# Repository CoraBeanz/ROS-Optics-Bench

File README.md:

<p align="center">
  <img src="docs/images/hero.svg" width="100%" alt="Self-Aligning Laser-to-Fiber Bench. Seen from above, a 635 nm laser beam passes an aperture, two polarizers and a beamsplitter, folds off two motorized mirrors, M1 and M2, and is focused into a single-mode fiber. M1 gets knocked, the focused spot slides off the fiber's core and the coupling drops to almost nothing; M2's motors search until the light comes back, then both mirrors walk the beam back to its peak. A fiber-face inset shows the spot stepping outward in a square spiral beside the core until it finds it, and a chart plots the output-to-reference photodiode ratio, as a share of its peak, through the knock and the recovery, replayed from the bench twin simulator.">
</p>

<h3 align="center">A mostly 3D-printed optical bench that couples a 635 nm laser into an optical fiber by itself. Knock a mirror out of line and four stepper-driven adjusters steer the beam back to peak coupling, with no hands on the knobs.</h3>

<p align="center">

</p>

<p align="center">
  <a href="#how-it-works"><b>How it works</b></a> ·
  <a href="#the-bench"><b>The bench</b></a> ·
  <a href="#optical-path"><b>Optical path</b></a> ·
  <a href="#auto-align"><b>Auto-align</b></a> ·
  <a href="#electronics"><b>Electronics</b></a> ·
  <a href="#software"><b>Software</b></a> ·
  <a href="#roadmap"><b>Roadmap</b></a> ·
  <a href="docs/bom/README.md"><b>Parts list</b></a>
</p>

## How it works

Getting a laser into a single-mode fiber means landing a focused spot on a core a few microns across, at the right angle. By hand that takes two kinematic mirrors, four knobs and a lot of patience. Here a NEMA 8 stepper turns each knob, and two photodiodes tell the motors how close they are.

| 1 · Score the coupling | 2 · Find the light | 3 · Steer and walk |
|---|---|---|
| A beamsplitter sends part of the laser to a reference photodiode, and the fiber's output lands on a second one. Their ratio is the score, so laser flicker cancels out. | After a knock the spot has usually left the core and the output reads nothing. M2 steps the spot outward in a square spiral until the output photodiode sees light again. | M2 alone moves the spot across the core. M1 with a matched, opposite M2 move changes only the angle. Alternating the two climbs the long, thin peak that one-knob-at-a-time adjusting stalls on. |

## The bench

<table>
  <tr>
    <td width="50%" valign="top">
      
      <br><sub>Laser, polarizer and beamsplitter, then M1 and M2, each with two NEMA 8 motors turning its adjusters through brass couplers and hex rods.</sub>
    </td>
    <td valign="top">

**Light.** A 635 nm Quarton laser module under 1 mW, trimmed by a 2 mm printed aperture and dimmed by two crossed polarizers.

**Steering.** Two 1 in mirrors in Thorlabs KMS-style kinematic mounts. A NEMA 8 stepper turns each 100 TPI adjuster through a brass coupler and a 2 mm hex rod: four motorized axes, 79 nm of screw travel per microstep.

**Focus.** An f = 8 mm asphere on a micrometer stage focuses the beam onto a fixed FC bulkhead. The lens moves; the fiber stays put.

**Sensing.** BPW34 photodiodes on MCP6002 transimpedance amps, read by a 16-bit ADS1115.

**Control.** An ESP32 Feather V2 drives four TMC2209s on one UART bus and takes plain-text commands over USB from a desktop test panel or from ROS 2 on a Jetson.

**Base.** Printed breadboard tiles on a 25 mm hole grid, so parts come off and go back in the same place.

  </td>
  </tr>
</table>

The full CAD model is one STEP file exported from Onshape with its subassembly tree, [`cad/assemblies/ros_laser_bench_main_assembly.step`](cad/assemblies/README.md). Every part to buy, print or check is in the [parts list](docs/bom/README.md) (source: `docs/bom/bom.csv`).

## Optical path

The beam folds in a Z. M1 and M2 sit 150 mm apart, and M2 is 310 mm from the lens, so tilting the two mirrors together can set both where the beam crosses the lens and the angle it arrives at, and through them where the focused spot lands on the fiber face and the angle it enters at. One microstep tilts a mirror by about 4.6 µrad. One turn of M2's X adjuster moves the spot about 230 µm across the fiber face, and one turn of its Y adjuster about 165 µm, because at a 45° fold a vertical tilt bends the beam by √2 times the tilt instead of twice it.

The 2 mm aperture does mode matching. The laser's 7 x 3 mm beam is much bigger than the single-mode fiber's mode seen at the lens (1.5 mm across), so only its centre can couple. In the bench twin 83% of the light through the aperture couples, against 25% of the whole beam without it. The fiber gets about a quarter of the laser's power either way, but with the aperture the light that could never couple is stopped before the beamsplitter, so the out/ref score at the peak is 0.67 instead of 0.20. In phase 1 the OV9281's bare sensor takes the lens's place, and with the two irises it lets the mirrors put the beam on the lens axis by spot position before the lens and fiber go in.

## Auto-align

With a single-mode fiber the coupling depends on where the spot lands on the core (set by the beam's angle at the lens) and on the angle it comes in at (set by the beam's offset at the lens). The first is about 25 times more sensitive, and both mirrors change both, so in motor coordinates the peak is a ridge 23 times longer than it is wide, running diagonally across M1 and M2. Turning one knob at a time crawls along it. Auto-align, in the [test panel](#bench-test-panel) and as a [ROS 2 action](#ros-2-on-the-jetson), uses the two moves people use by hand instead:

- **Find.** If the output photodiode sees nothing, M2 steps the spot outward in a square spiral, up to **Search (turns)** either way, until the out/ref ratio clears 2% of its aligned value.
- **Steer.** M2 alone moves the spot across the core: the narrow direction, 25 microsteps to the 1/e point on M2X.
- **Walk.** M1 plus a matched, opposite M2 move keeps the spot where it is and changes only the angle: the wide direction, about 580 microsteps of M1.
- **Repeat** walk and steer on both planes until a sweep gains less than 0.3%. Each line search approaches its points from the same side, so the play in the hex couplings always sits the same way.

The first run on a fiber also measures the walk directions on the real bench, since they depend on motor directions and lever arms. In 100 simulated knocks of 0.3 to 3 mrad, steer and walk brought all 100 back above 99.9% of the best coupling, with a median of 19 s and a worst case of 66 s. One motor at a time got 59 back to 90%. Everything here comes from the [bench twin](#bench-twin-simulator); Auto-align hasn't run on the hardware yet.

## Electronics

| Part | Role |
| --- | --- |
| Adafruit ESP32 Feather V2 | Real-time side: steppers, soft limits, photodiode sampling, laser |
| 4x Adafruit TMC2209 breakout on one UART bus | Stepper drivers: 3200 microsteps per adjuster turn, StealthChop, current set over UART |
| ADS1115 (16-bit ADC) + 2x BPW34 photodiode on an MCP6002 transimpedance amp (47 kΩ) | Reference and output power |
| 12 V supply | Motor power; the Feather runs from USB |
| Jetson (ROS 2) | Camera, optimizer, experiment control |
| Arducam OV9281 (global shutter, UVC) | Bare-sensor beam profiler for phase 1 |

<table>
  <tr>
    <td width="58%"></td>
    <td width="42%"></td>
  </tr>
  <tr>
    <td><sub>Control board, 100 x 100 mm, two layers. The Feather, the four TMC2209 breakouts and the ADS1115 plug in.</sub></td>
    <td><sub>Photodiode amp, 34 x 25 mm. Build two: reference and output.</sub></td>
  </tr>
</table>

Both boards are KiCad 10 projects generated from Python, all through-hole, with Gerbers ready to order in [electronics/pcb](electronics/pcb/README.md). Every cable on the bench is in [electronics/system_wiring.svg](electronics/system_wiring.svg), and the full pin table is in [electronics/wiring.md](electronics/wiring.md).

## Software

Where each piece lives, and how far it has been run:

| Module | What it does | Run so far |
| --- | --- | --- |
| [`firmware/optics_bench`](#building-the-firmware) | Arduino IDE sketch for the ESP32: four axes with soft limits and positions kept in flash, auto-ranging photodiode sampling, the laser, and the serial protocol | On the bench: laser, all four motors and both photodiodes |
| [`tools/test_gui.py`](#bench-test-panel) | Dark-mode PySide6 test panel: jog, go-to, photodiode readout and plots, CSV logging and Auto-align; `--sim` runs it on the bench twin | On the bench; Auto-align on the simulator only |
| [`tools/bench_twin`](#bench-twin-simulator) | Physical model of the bench and the Aligner both front ends run; `tools/twin.py` runs trials and draws figures | 14 unit tests |
| [`host/ros2_ws`](#ros-2-on-the-jetson) | ROS 2 Humble packages for the Jetson: the bench as topics, services and actions, Align as an action, and a beam-spot node for the OV9281 | Against the simulator on Humble |

### Building the firmware

1. In the Arduino IDE, install the ESP32 boards package (Boards Manager, "esp32" by Espressif).
2. Install the libraries below with the Library Manager.
3. Open `firmware/optics_bench/optics_bench.ino`.
4. Select your ESP32 board and port, then Upload. Serial Monitor runs at 115200 baud with newline line endings.

Code in `src/` is compiled with the sketch automatically. Record any library added through the Library Manager here so the build can be reproduced.

| Library | Version | Used for |
| --- | --- | --- |
| TMCStepper (teemuatlut) | 0.7.3 | TMC2209 register setup over UART |
| AccelStepper (Mike McCauley) | 1.64 | Ramped STEP/DIR motion |

The ADS1115 photodiode ADC is read with the ESP32 core's own Wire library (`src/sensing/sensing.cpp`), so it needs no library of its own. Firmware 0.1.0 used Adafruit ADS1X15 2.6.2 and Adafruit BusIO for it; they can stay installed but are no longer used.

The firmware was last built with the esp32 boards package 3.3.7.

Every pin is set in `firmware/optics_bench/config.h`. The wiring diagram and full pin table for the Feather ESP32 V2, the four Adafruit TMC2209 breakouts, the laser, the ADS1115 and the two photodiode amplifier boards are in [electronics/wiring.md](electronics/wiring.md). The serial protocol is plain text and documented in `firmware/optics_bench/src/comms/protocol.h`, so the Serial Monitor or the Jetson can use the same commands.

### Bench test panel

`tools/test_gui.py` is a small desktop app for the bench tests: laser on/off, jog, nudge and go-to for the four mirror motors, and live photodiode readings. It is a dark-mode Qt window built on PySide6 (the LGPL Qt binding) and pyserial, both listed in `tools/requirements.txt`.

```
py -3 -m pip install -r tools/requirements.txt
py -3 tools/test_gui.py          # pick the ESP32's COM port, Connect
py -3 tools/test_gui.py --sim    # try it without hardware
```

`py -3` picks the regular Python install on Windows; a bare `python` can resolve to another bundled interpreter such as KiCad's.

- **Positions** are in microsteps, 3200 per adjuster turn. One turn of a 100 TPI adjuster is 254 um, so a full step is about 1.3 um of screw travel.
- **Zero and soft limits.** "Reset to 0" on a motor's row calls its current knob position zero without moving it, and "Reset all to 0" does all four. Use them whenever the stored position has stopped matching reality, for example after turning an adjuster by hand. The soft limits (default -3 to +3 turns, adjustable up to +-8) stay relative to zero, because the hex bit only has about 4 turns of engagement one way. Positions and limits are saved to flash and survive a power cycle. If power drops while a motor is moving, or a motor moves and its driver loses its 12 V before the firmware next sees it working (it checks a few seconds after the motors stop), that motor's position is marked untrusted: the panel warns that positions may be off, and the firmware's boot message names the motors. The mark is kept in flash across reboots until you reset that motor ("Reset to 0") or all four. A 12 V cycle while the motors sit still only warns: the positions are kept, and each motor may settle up to 2 full steps (about 2.5 um of screw travel) away when it is next powered.
- **Coil release.** A motor is powered only while it moves: it is released 0.5 s after it stops, so the motors stay cool between moves, and the non-back-driving adjuster screws hold the mirror. The **On** box shows whether a motor is powered; ticking it holds that motor powered until you untick it. `AUTO_RELEASE` in `config.h` turns this off.
- **Hold-to-jog** (the double arrows) keeps a motor running while the button is held. The firmware stops it by itself if the panel stops refreshing the jog, so a crashed GUI can't run a motor to its limit.
- **Keys:** arrows move M1 (Left/Right = M1X, Down/Up = M1Y), A/D and S/W move M2X and M2Y by the selected step, L toggles the laser, Esc stops everything.
- **Diag** shows the TMC2209 status (current, StealthChop, overtemperature, short and open-load flags). A driver that doesn't answer on the UART shows a red dot and refuses to move. Between moves the firmware checks one driver every 0.25 s, so a driver that loses its 12 V turns red within about a second.
- **Auto-align.** Pick the fiber on the bench and press **Align**. It finds the light, then peaks the out/ref ratio by steering with M2 and walking M1 and M2 together (see [Auto-align](#auto-align)). The first run after connecting or switching fiber also measures the walk directions, so start it near the peak; the panel keeps them until it disconnects. Later runs recover from wherever the beam is, for example after a knock. If there is no light on the output photodiode, it first searches with M2 up to **Search (turns)** either way (default 0.4 turn: about ±90 µm across the fiber face and ±65 µm up and down; one turn of M2X moves the spot about 230 µm, one turn of M2Y about 165 µm). The search covers a square, so its time grows with the square of that number, and the log says how many points it will visit. Soft limits still stop any move that would pass them. **Stop** or Esc ends it. It uses the same serial commands as the rest of the panel, but it has only been run against the simulator so far.
- **Photodiodes.** Tick **Live** to stream the reference and output photodiode voltages (5 to 50 readings a second, each the average of all ADC samples since the last one). The panel shows each voltage with its photocurrent and optical power, the output/reference ratio with the best ratio seen and the motor positions where it happened, and a rolling plot (log scale optional). **Measure dark** switches the laser off briefly, records the offsets and subtracts them from then on. **ADC range** fixes the ADS1115 gain instead of auto-ranging, and **Save CSV** writes up to the last 30,000 readings (10 minutes at 50 a second).
- **Simulator.** `--sim` (or the Simulator port) runs the bench twin behind the same serial commands: the photodiodes read what the modelled optics couple into the chosen fiber, with the best position hidden a little way from zero. **Knock M1** and **Knock M2** tilt a mirror by 0.5 to 2 mrad as if bumped, **Unknock** takes the knocks out, and **Peak?** shows where the best position is. Knock, then Align, to watch it recover. The same commands work from the console as `SIM KNOCK M1 [mrad]`, `SIM PEAK`, `SIM FIBER sm630` and `SIM RESET`.

#### First power-up checklist

1. Flash the firmware and connect. A driver whose 12 V supply is off doesn't answer on the UART, so it shows a red dot, and a move on that axis is refused with "driver offline".
2. With the 12 V supply on, send `REPROBE ALL` (or just move the axis, which retries). The dots should go green, and the REPROBE reply should end in `slots=ok` (the connection bar picks it up on the next `INFO`). Switching the 12 V on after USB like this is fine, and so is switching it off between sessions with USB left on: the positions are kept, though each driver's microstep counter restarts, so a motor may settle up to 2 full steps away when it is next powered. Only a motor that was moving, or had just moved, when its 12 V went away is marked untrusted until you reset it.
3. Take the hex bits out of the adjusters and nudge each motor by 1/4 turn to check which way positive turns. Flip it with `invert` in `config.h` if needed.
4. Refit the bits, press "Reset all to 0", and start aligning.
5. With the ADS1115 and photodiode boards connected, the photodiode panel should show `ADC: ok`. Cover each diode and shine a light on it to check its channel, then press **Measure dark** with the room lit as it will be during runs. If the ADS1115 stops answering later (a loose STEMMA QT cable), the firmware drops the failed readings instead of reporting 0 V, warns `ADS1115 stopped answering` after 10 failures in a row, and stops reading it until the next photodiode request finds it again.

### Bench twin (simulator)

`tools/bench_twin` is a small physical model of the bench, used to size and test the alignment routine before the hardware can. It models:

- **Optics:** the 7 x 3 mm laser beam cut by the 2 mm aperture, the two mirrors 150 mm apart, iris 2 at 3 mm, and the f = 8 mm lens. Single-mode coupling is the overlap of the laser field with the fiber mode, including the aperture's hard edge. Multimode coupling is the share of the focused spot that the core accepts.
- **Motors:** 100 TPI adjusters on a 17.3 mm lever and a little play in each hex coupling. The randomized benches the simulator and the trials use also add a little crosstalk between each mount's two axes.
- **Photodiodes:** the reference and output photodiodes through the ADS1115, with noise and dark offsets.
- **Knocks:** a bumped mirror mount tilts by an amount the motors don't know about.

```
py -3 tools/twin.py                       key numbers (--fiber sm630, mm50 or smf28)
py -3 tools/twin.py ceiling               best coupling vs aperture size and lens focal length
py -3 tools/twin.py trials -n 100 --compare   knock a mirror and recover, 100 times, both methods
py -3 tools/twin.py landscape             redraws docs/images/twin_landscape.png (needs matplotlib)
py -3 -m unittest discover tools/tests
```

What it says so far, for the single-mode fiber:

- **The peak is narrow and diagonal.** Moving M2X alone, coupling falls to 1/e within 25 microsteps (1.5 full steps). Moving M1 and M2 together the opposite way ("walking"), it stays up for about 580 microsteps. So in motor coordinates the peak is a long, thin ridge, 23 times longer than it is wide, running diagonally across M1 and M2. Adjusting one motor at a time stalls part-way along it.
- **Recovery.** In 100 simulated knocks of 0.3 to 3 mrad on a random mirror, steer and walk got all 100 back above 99.9% of the best coupling, with a median of 19 s and a worst case of 66 s (at 60 RPM and 600 RPM/s). One motor at a time got 68 of 100 back to 90%, and its worst case ended at 35%. Most of the time goes into finding the light again. Knocks of M1 above about 5 mrad can defeat the search even though M2 could still put the spot back on the core: the beam then crosses the lens about 1.5 mm off axis and enters the fiber too steeply, so M2 alone brings back under 3% of the peak and the spiral never sees light (11 of the 46 M1 knocks in a run of 100 knocks of 3 to 6 mrad). A larger **Search (turns)** doesn't help these.
- **The 2 mm aperture is close to ideal for coupling efficiency.** With the f = 8 mm lens, 83% of the light that gets through it can be coupled. The best combination tried reaches 86% (a 2.5 mm aperture with f = 11 mm), and 2 mm with f = 9 mm gets 85%. Without the aperture only 25% couples, because the 7 x 3 mm beam is much bigger than the fiber mode seen at the lens (1.5 mm). The aperture passes only 30% of the beam, so the fiber gets about a quarter of the laser's power either way; what it changes is the out/ref ratio at the peak, 0.67 instead of 0.20, since the reference photodiode sits after it.
- **The play in the hex couplings matters.** One degree of play is about 9 microsteps, a third of the single-mode peak's width. Each line search in the routine therefore approaches its points from one side.

The numbers rest on estimates to replace with bench measurements, all set in `tools/bench_twin/bench.py` and `optics.py`:

| Estimate | Value used | How to measure |
| --- | --- | --- |
| Adjuster lever arm | 17.3 mm (from the 24.5 mm motor spacing) | Scan M2X across the peak; the width scales with it |
| Play per hex coupling | 1 degree (9 microsteps) | Hysteresis test: approach the same point from both sides |
| Laser beam | 7 x 3 mm across (taken as the 1/e^2 width) | Camera or knife edge |
| Fiber mode | 4.2 um across (630HP) | Datasheet |
| Lens clear aperture | 5 mm | The lens listing |
| Beamsplitter, laser power, polarizer setting | 50/50, 0.9 mW, 30% | Photodiode volts |

The banner at the top of this page replays one of these runs: M1 knocked 1.5 mrad on the single-mode fiber, recovered in 17 s. The figures are drawn by the scripts in [`docs/images/src`](docs/images/src/common.py); the banner and the Auto-align figure run the twin to get their numbers.

### ROS 2 on the Jetson

`host/ros2_ws` holds ROS 2 Humble packages for the Jetson: a driver node that puts the ESP32 (or the simulator) on ROS topics, services and actions, with Align as an action; a node that finds the laser spot on the OV9281; and launch files. They use `tools/bench_link.py` and `tools/bench_twin` directly, so they align the same way the test panel does. Setup and usage: [host/ros2_ws/README.md](host/ros2_ws/README.md).

```
ros2 launch optics_bench_bringup bench.launch.py                          # on the simulator
ros2 launch optics_bench_bringup bench.launch.py port:=/dev/optics_bench  # on the bench
```

## Roadmap

The laser, all four mirror motors and both photodiodes (on hand-wired amplifiers for now) work on the bench, and first fiber coupling by hand is under way. The PCBs are designed but not ordered yet. Auto-align and the ROS 2 packages have run only against the bench twin so far, and the ROS 2 packages haven't run on the Jetson, the ESP32 or the camera yet.

- [x] Bench CAD in Onshape: printed base, motor-mirror assemblies, optics mounts ([`cad/`](cad/assemblies/README.md))
- [x] Firmware for the laser, the four mirror motors and both photodiodes, and the [test panel](#bench-test-panel), running on the bench
- [x] [Bench twin](#bench-twin-simulator) and Auto-align, tested in simulation over hundreds of knocks
- [x] [ROS 2 Humble packages](#ros-2-on-the-jetson), run against the simulator
- [x] Control board and photodiode amp PCBs designed, with Gerbers ready ([`electronics/pcb`](electronics/pcb/README.md))
- [ ] **Phase 1, beam steering:** the camera and the two irises put the beam on a known axis by spot position
- [ ] **Phase 2, fiber coupling:** swap the camera for the lens and fiber and climb to maximum coupled power, multimode first, then single-mode
- [ ] **Phase 3, the demo:** bump a mirror and watch it recover on the real bench
- [ ] PCBs ordered and built, and ROS 2 running on the Jetson

## Stack

| Layer | Built with |
|---|---|
| **Optics** | 635 nm diode laser, 2 mm aperture, crossed polarizers, 1 in mirrors in kinematic mounts, f = 8 mm asphere, FC fiber |
| **Mechanics** | 3D-printed mounts and base designed in Onshape; NEMA 8 steppers, brass couplers and hex rods on 100 TPI adjusters |
| **Electronics** | ESP32 Feather V2, TMC2209 drivers, ADS1115 and BPW34 photodiodes on MCP6002 amps; KiCad 10 boards generated from Python |
| **Firmware** | C++ Arduino IDE sketch on the ESP32: TMCStepper, AccelStepper, plain-text serial protocol |
| **Desktop** | Python, PySide6 and pyserial: the dark-mode test panel |
| **Simulation** | Python and numpy: Gaussian-beam coupling, motors with play, photodiodes, and the Aligner |
| **Robotics** | ROS 2 Humble on a Jetson: driver node with Align and MoveTo actions, v4l2_camera and a beam-spot node |

## Repository layout

```
cad/
├── assemblies/            the whole bench as one STEP from Onshape, and its README
├── parts/pcb/             STEP models and 3D renders of the two PCBs
└── print/, vendor/        placeholders for print-ready files and purchased-part models
docs/
├── bom/                   parts list: bom.csv, and the README tools/make_bom_md.py generates from it
└── images/                README figures; images/src/ holds the scripts that draw the SVGs
electronics/
├── wiring.md, wiring.svg  pin table and wiring diagram for the Feather, drivers, laser, ADC and amps
├── system_wiring.svg      every cable on the bench
└── pcb/                   KiCad projects (control board, photodiode amp), their generator and fab outputs
firmware/optics_bench/     Arduino IDE sketch for the ESP32
├── optics_bench.ino       setup() and loop()
├── config.h               pin map, bus addresses, motor limits
└── src/                   motion (drivers, soft limits), sensing (ADS1115), laser, comms (protocol)
host/ros2_ws/              ROS 2 Humble workspace for the Jetson: driver, camera, interfaces, bringup
tools/
├── test_gui.py            the bench test panel
├── bench_link.py          serial and simulator links to the controller, shared by the panel and ROS
├── bench_twin/            the bench simulator and the Aligner
├── twin.py                trials, coupling ceiling, landscape figure
├── tests/                 unit tests for the twin and the Aligner
└── make_bom_md.py         writes docs/bom/README.md from bom.csv
```

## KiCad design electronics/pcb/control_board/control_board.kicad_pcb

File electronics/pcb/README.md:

# Circuit boards

Two KiCad 10 projects replace the perfboard wiring:

| Board | Size | What it does |
| --- | --- | --- |
| [control_board](control_board) | 100 x 100 mm, 2 layers | Carrier for the ESP32 Feather V2, the four TMC2209 breakouts and the ADS1115. Adds the 12 V input protection, a VM feed for each driver, laser and photodiode plugs, and a test header for the Analog Discovery 3. |
| [pd_amp](pd_amp) | 34.3 x 25.4 mm, 2 layers | Photodiode amplifier: BPW34 into an MCP6002 transimpedance amp. Build two, one for the reference diode and one for the fiber output. |

How it all connects: [../system_wiring.svg](../system_wiring.svg) and [../wiring.md](../wiring.md).

## Why a carrier board and not chip-down parts

The Feather, the TMC2209 breakouts and the ADS1115 plug into female headers. The TMC2209 breakouts keep their screw terminals: each one plugs in by its 10-pin logic header only, with the terminals along the board's top or bottom edge and the wire entries facing out. The carrier board itself only has through-hole parts that cost a few dollars in total, and it fits the cheapest price tier at JLCPCB and PCBWay (100 x 100 mm, 2 layers).

- The breakouts are already on hand, and this firmware already runs on them.
- A chip-down TMC2209 is a QFN-28 with a thermal pad. It needs fab assembly and its own layout checks (sense resistors, charge pump, thermal vias), and a board with an ESP32 module would need the USB and boot circuits too. That is a second board bring-up for no gain on a four-motor bench.
- A failed driver or Feather is swapped by unplugging it.
- Every pin matches `firmware/optics_bench/config.h`, so the firmware doesn't change.

## Ordering

Upload `fab/<board>/<board>_gerbers.zip` as-is. Defaults are fine: 2 layers, 1.6 mm FR-4, 1 oz copper, HASL, any mask colour. The zip holds the copper, mask, silkscreen, outline and one Excellon drill file. There are no SMD parts, so no stencil or assembly files are needed.

Parts: `fab/<board>/<board>_bom.csv`. All the parts are through-hole and stocked at DigiKey, Mouser and LCSC. The part numbers are suggestions, and any part with the same footprint fits.

## Assembly notes (control board)

1. Solder the low parts first: R1, R2, D1-D3, F1, then J10, the JST-XH plugs, J5, J6 and the capacitors (mind the + marks).
2. Solder the female headers for A1 (16 + 12 pins), U1-U4 (10 pins each) and A2 (10 pins). Plug the boards in while soldering so the headers stay straight.
3. The TMC2209 breakouts keep their screw terminals. Each one plugs in by its logic header, with the terminal edge at the board edge. Two M2 x 11 mm standoffs under the terminal-end mounting holes (marked M2 on the board) hold that end up while you tighten the screws. Check the standoff height against your header stack (about 8.5 mm socket plus the 2.5 mm plastic of the male header).
4. Wire each motor straight into its breakout's 1A/1B/2A/2B terminals. Run a 2-wire lead from the carrier's VM plug next to the driver (J1-J4, pin 1 = +12 V, pin 2 = GND, marked + -) into the breakout's VM + and GND terminals.
5. The UART addresses are set by the board: U1 = 0 (M1X), U2 = 1 (M1Y), U3 = 2 (M2X), U4 = 3 (M2Y). Put each breakout in its own slot.
6. Before plugging anything in, power J5 or J6 with 12 V and check that D3 lights, that J1-J4 read about 11.5 V (after the Schottky), and that 3V3 isn't shorted to GND.

## Connectors

Control board:

| Ref | Type | Pins |
| --- | --- | --- |
| J1-J4 | JST-XH 2 | VM feed for the M1X, M1Y, M2X and M2Y breakouts: 1 = +12 V, 2 = GND. A short lead goes to the breakout's VM + / GND screw terminals |
| U1-U4 terminals | Breakout screw terminals, 2.54 mm | Motor coils: 1A/1B = coil A, 2A/2B = coil B, plus VM + / GND from J1-J4 |
| J5 | Screw terminal, 5.08 mm | 12 V in: + and - (marked) |
| J6 | Barrel jack 5.5 x 2.1 mm | 12 V in, centre positive (same net as J5, so use one of them) |
| J7 | JST-XH 3 | Laser: 1 = 3V3, 2 = TTL (GPIO 21), 3 = GND |
| J8 | JST-XH 3 | Reference photodiode board: 1 = 3V3, 2 = PD_REF (ADS1115 A0), 3 = GND |
| J9 | JST-XH 3 | Output photodiode board: 1 = 3V3, 2 = PD_OUT (ADS1115 A1), 3 = GND |
| J10 | 1x10 pin header | Test: 1 GND, 2 3V3, 3 SCL, 4 SDA, 5 UART bus, 6 LASER TTL, 7 PD_REF, 8 PD_OUT, 9 ADS1115 A2, 10 A3 |
| A1 | Feather V2 socket | USB-C faces the top edge |

Photodiode board: J1 (JST-XH 3) is 1 = 3V3, 2 = VOUT, 3 = GND, which matches J8 and J9, so the cable is wired 1:1.

## Design notes

- **12 V input.** A 2 A PTC fuse (F1), a 1N5822 Schottky in series for reverse polarity (about 0.4 V drop), an 18 V bidirectional TVS (D2), 470 uF bulk capacitance, and 100 uF at each driver's VM plug, on top of the breakout's own 22 uF. The motor current is well under 1 A in total at 350 mA RMS per motor.
- **Ground.** Both layers are ground pours, stitched with vias. The photodiode signal returns through the pour straight back to the ADS1115.
- **DIAG.** Each driver's DIAG output goes to an input-only Feather pin (M1X to I34/A2, M1Y to I39/A3, M2X to I36/A4, M2Y to I37). The firmware doesn't read them yet, so they're there for stall detection later. INDEX isn't connected.
- **Tracks.** Signals are 0.3 mm, 3V3 is 0.5 mm and 12 V is 1.0 mm, and a 0.4 mm ground tree runs under the pours. Motor current never crosses the carrier: it goes from the breakout's terminals straight to the motor. The clearance is 0.2 mm, or 0.3 mm on 12 V. Every rule is in the `.kicad_pro` files.
- **Mounting.** The control board has an M3 hole in each corner, 93 mm apart, which doesn't land on the bench's 25 mm insert grid, so it needs a printed plate or standoffs. The photodiode board has two M3 holes 25 mm apart, centred on the BPW34, so it bolts straight onto the grid.

## Regenerating

The schematics and boards are generated from `gen/design.py`, which is the only place parts, pins and positions are defined. After editing it:

```
py -3 electronics/pcb/gen/build.py
```

The generators look for KiCad in `C:/Users/Vince/AppData/Local/Programs/KiCad/10.0`. To use another install, set `KICAD_DIR`.

That runs, in order:

1. `make_lib.py`: the custom symbols and socket footprints in `lib/`.
2. `make_sch.py`: the schematics.
3. `kicad-cli`: the netlist.
4. `make_pcb.py` (KiCad's Python): placement, routing and ground pours.
5. ERC, and DRC with schematic parity.
6. The fab outputs in `fab/`.

It stops with an error if ERC or DRC finds anything or a net is left unrouted. A board with ERC or DRC errors keeps its previous `fab/<board>/` files, so the zip there is always the last good build; the reports go to `fab/<board>_check/`. The router is a small A* grid router in `gen/route.py`.

To open a board in KiCad and edit it by hand, open `control_board/control_board.kicad_pro`. A rerun of `build.py` overwrites manual edits, so once the board is being edited by hand, stop regenerating it.

## Open assumptions

- The breakout's screw terminals take wires from the breakout's outer edge, so with the terminal edge on the board edge the wires come in from outside the board. Check the direction on one breakout. If the entries face the other way, swap each pair of driver slots in `gen/design.py`.
- The M2 standoff holes sit under the breakout's terminal-end mounting holes, taken from Adafruit's board file.
- The ADS1115 is the Adafruit 1085 layout (one 10-pin header, board above it). The newer STEMMA QT version has the same header order.
- The Jetson is the USB host for the Feather and the camera.

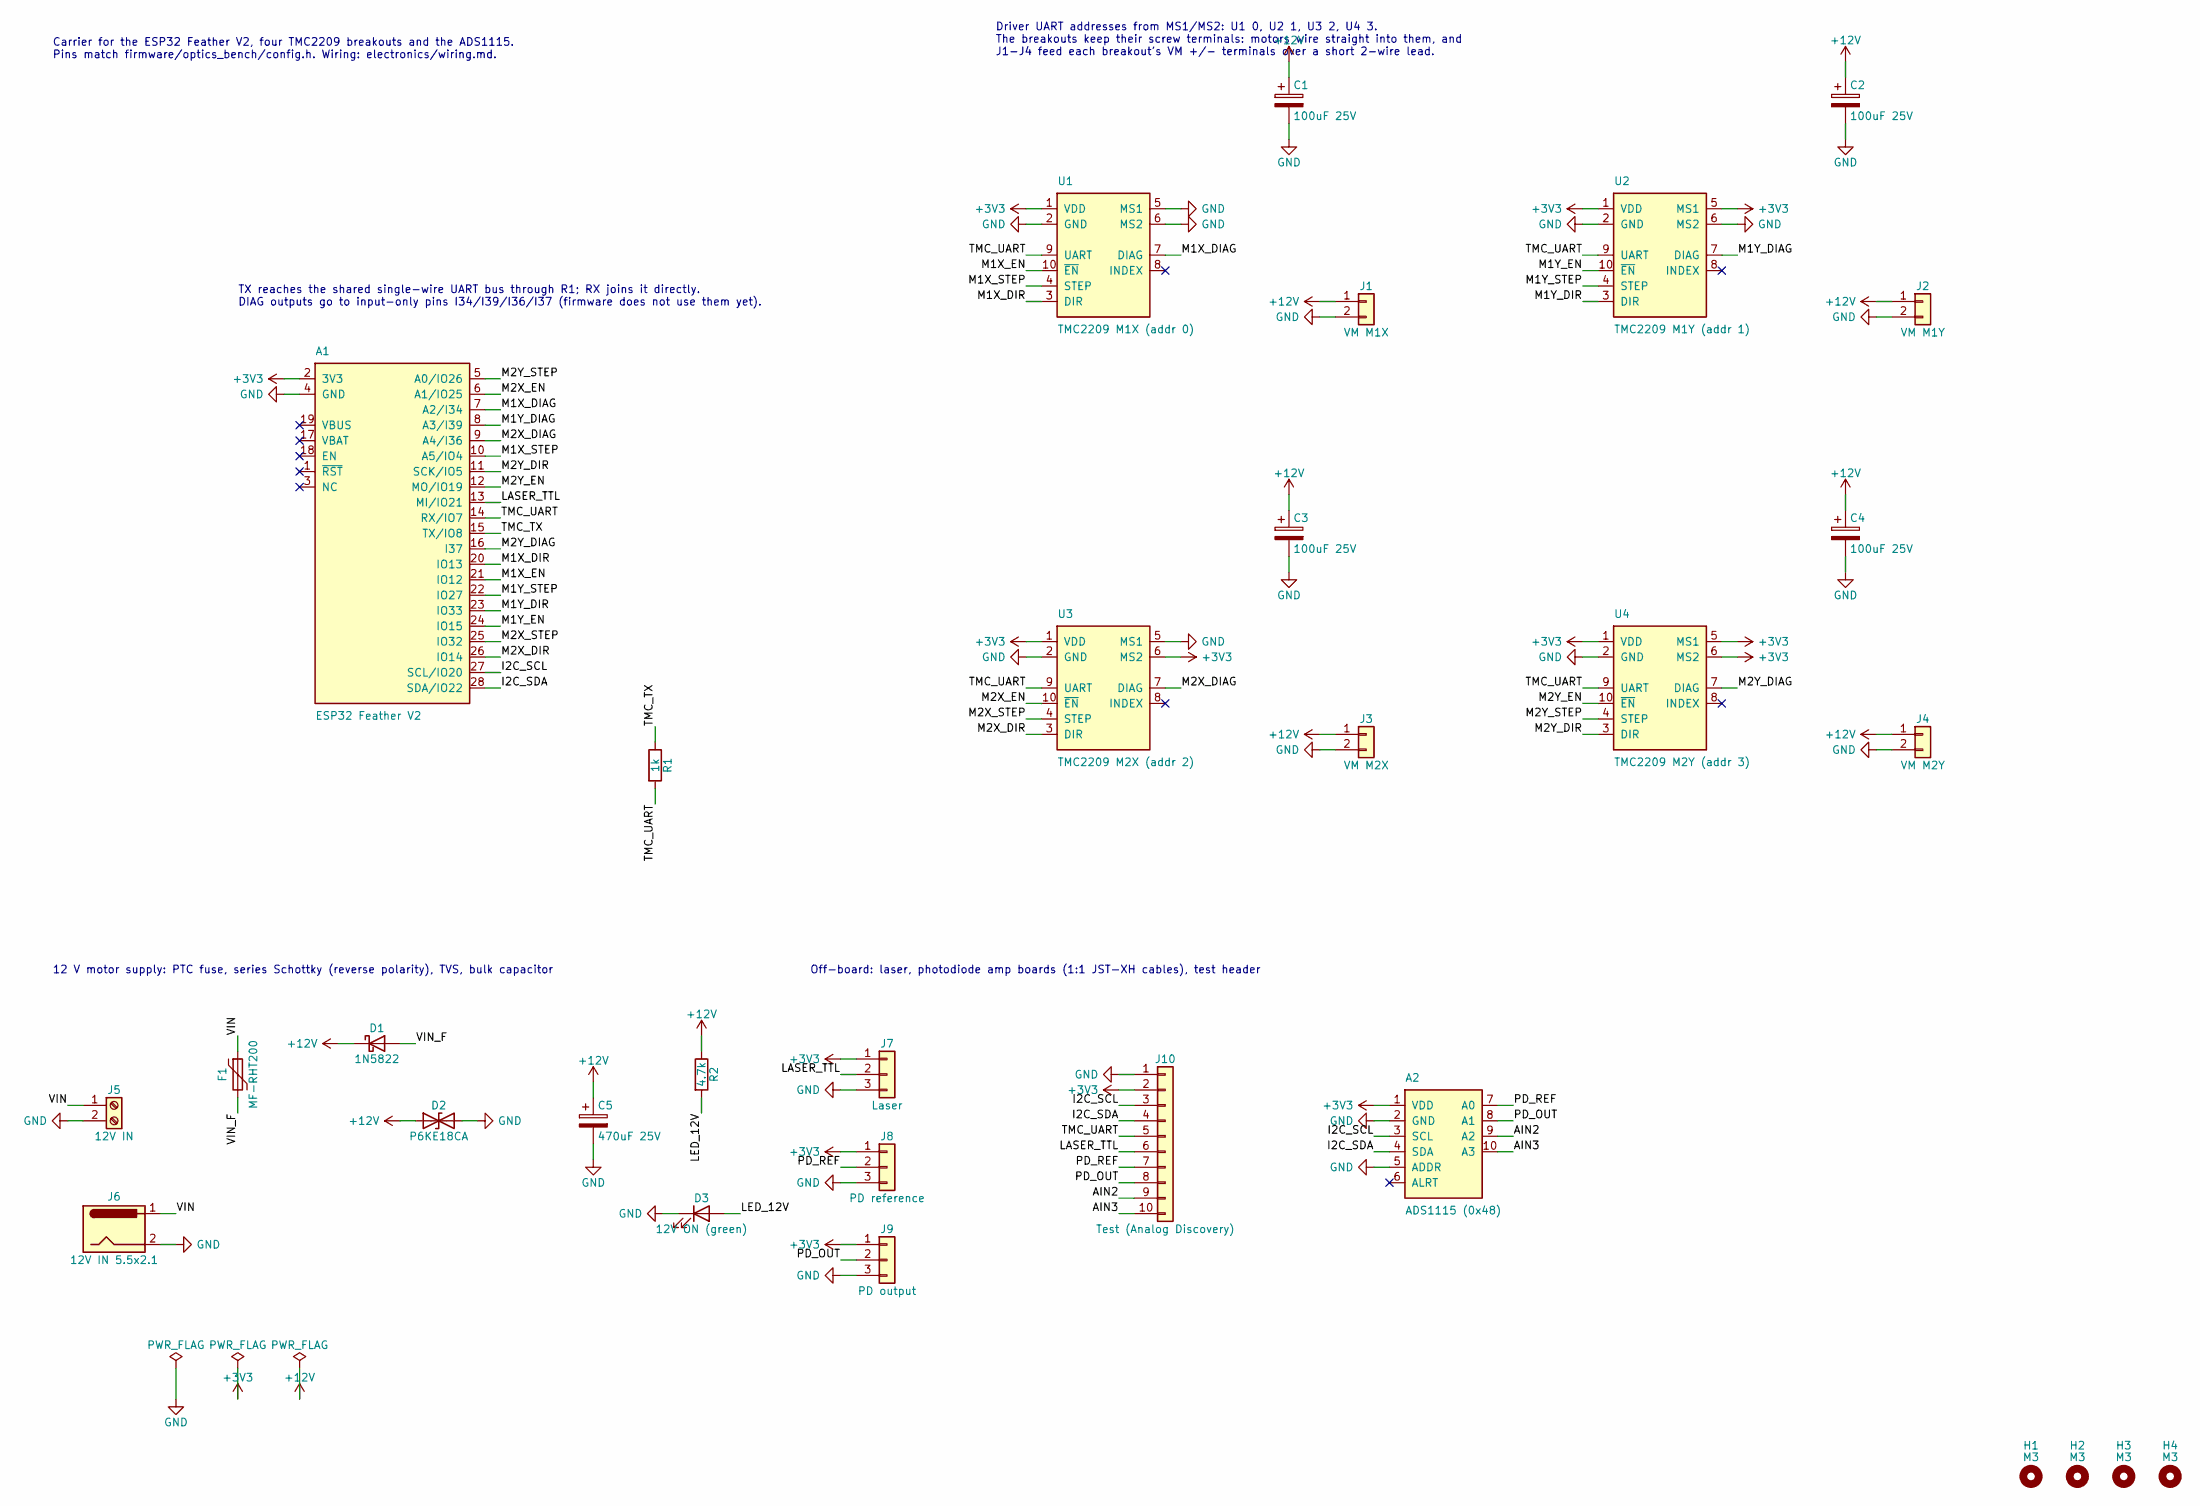
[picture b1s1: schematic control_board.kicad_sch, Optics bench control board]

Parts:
A1: ESP32 Feather V2; Adafruit_Feather_ESP32_V2_Socket
A2: ADS1115 (0x48); Adafruit_ADS1115_Socket
C1, C2, C3, C4: 100uF 25V; CP_Radial_D6.3mm_P2.50mm
C5: 470uF 25V; CP_Radial_D10.0mm_P5.00mm
D1: 1N5822; D_DO-201AD_P15.24mm_Horizontal
D2: P6KE18CA; D_DO-15_P10.16mm_Horizontal
D3: 12V ON (green); LED_D3.0mm
F1: MF-RHT200; Fuse_Bourns_MF-RHT200
H1, H2, H3, H4: M3; MountingHole_3.2mm_M3
J1: VM M1X; JST_XH_B2B-XH-A_1x02_P2.50mm_Vertical
J2: VM M1Y; JST_XH_B2B-XH-A_1x02_P2.50mm_Vertical
J3: VM M2X; JST_XH_B2B-XH-A_1x02_P2.50mm_Vertical
J4: VM M2Y; JST_XH_B2B-XH-A_1x02_P2.50mm_Vertical
J5: 12V IN; TerminalBlock_Phoenix_MKDS-1,5-2-5.08_1x02_P5.08mm_Horizont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
J6: 12V IN 5.5x2.1; BarrelJack_Horizontal
J7: Laser; JST_XH_B3B-XH-A_1x03_P2.50mm_Vertical
J8: PD reference; JST_XH_B3B-XH-A_1x03_P2.50mm_Vertical
J9: PD output; JST_XH_B3B-XH-A_1x03_P2.50mm_Vertical
J10: Test (Analog Discovery); PinHeader_1x10_P2.54mm_Vertical
R1: 1k; R_Axial_DIN0207_L6.3mm_D2.5mm_P10.16mm_Horizontal
R2: 4.7k; R_Axial_DIN0207_L6.3mm_D2.5mm_P10.16mm_Horizontal
U1: TMC2209 M1X (addr 0); Adafruit_TMC2209_Socket
U2: TMC2209 M1Y (addr 1); Adafruit_TMC2209_Socket
U3: TMC2209 M2X (addr 2); Adafruit_TMC2209_Socket
U4: TMC2209 M2Y (addr 3); Adafruit_TMC2209_Socket

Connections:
+3V3: A1.2 (3V3), A2.1 (VDD), J7.1, J8.1, J9.1, J10.2, U1.1 (VDD), U2.1 (VDD), U2.5 (MS1), U3.1 (VDD), U3.6 (MS2), U4.1 (VDD), U4.5 (MS1), U4.6 (MS2)
+12V: C1.1, C2.1, C3.1, C4.1, C5.1, D1.1 (K), D2.1 (A1), J1.1, J2.1, J3.1, J4.1, R2.1
/AIN2: A2.9 (A2), J10.9
/AIN3: A2.10 (A3), J10.10
/I2C_SCL: A1.27 (SCL/IO20), A2.3 (SCL), J10.3
/I2C_SDA: A1.28 (SDA/IO22), A2.4 (SDA), J10.4
/LASER_TTL: A1.13 (MI/IO21), J7.2, J10.6
/LED_12V: D3.2 (A), R2.2
/M1X_DIAG: A1.7 (A2/I34), U1.7 (DIAG)
/M1X_DIR: A1.20 (IO13), U1.3 (DIR)
/M1X_EN: A1.21 (IO12), U1.10 (~EN)
/M1X_STEP: A1.10 (A5/IO4), U1.4 (STEP)
/M1Y_DIAG: A1.8 (A3/I39), U2.7 (DIAG)
/M1Y_DIR: A1.23 (IO33), U2.3 (DIR)
/M1Y_EN: A1.24 (IO15), U2.10 (~EN)
/M1Y_STEP: A1.22 (IO27), U2.4 (STEP)
/M2X_DIAG: A1.9 (A4/I36), U3.7 (DIAG)
/M2X_DIR: A1.26 (IO14), U3.3 (DIR)
/M2X_EN: A1.6 (A1/IO25), U3.10 (~EN)
/M2X_STEP: A1.25 (IO32), U3.4 (STEP)
/M2Y_DIAG: A1.16 (I37), U4.7 (DIAG)
/M2Y_DIR: A1.11 (SCK/IO5), U4.3 (DIR)
/M2Y_EN: A1.12 (MO/IO19), U4.10 (~EN)
/M2Y_STEP: A1.5 (A0/IO26), U4.4 (STEP)
/PD_OUT: A2.8 (A1), J9.2, J10.8
/PD_REF: A2.7 (A0), J8.2, J10.7
/TMC_TX: A1.15 (TX/IO8), R1.1
/TMC_UART: A1.14 (RX/IO7), J10.5, R1.2, U1.9 (UART), U2.9 (UART), U3.9 (UART), U4.9 (UART)
/VIN: F1.1, J5.1, J6.1
/VIN_F: D1.2 (A), F1.2
GND: A1.4 (GND), A2.2 (GND), A2.5 (ADDR), C1.2, C2.2, C3.2, C4.2, C5.2, D2.2 (A2), D3.1 (K), J1.2, J2.2, J3.2, J4.2, J5.2, J6.2, J7.3, J8.3, J9.3, J10.1, U1.2 (GND), U1.5 (MS1), U1.6 (MS2), U2.2 (GND), U2.6 (MS2), U3.2 (GND), U3.5 (MS1), U4.2 (GND)

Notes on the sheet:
Carrier for the ESP32 Feather V2, four TMC2209 breakouts and the ADS1115. Pins match firmware/optics_bench/config.h. Wiring: electronics/wiring.md.
12 V motor supply: PTC fuse, series Schottky (reverse polarity), TVS, bulk capacitor
Off-board: laser, photodiode amp boards (1:1 JST-XH cables), test header
Driver UART addresses from MS1/MS2: U1 0, U2 1, U3 2, U4 3. The breakouts keep their screw terminals: motors wire straight into them, and J1-J4 feed each breakout's VM +/- terminals over a short 2-wire lead.
TX reaches the shared single-wire UART bus through R1; RX joins it directly. DIAG outputs go to input-only pins I34/I39/I36/I37 (firmware does not use them yet).

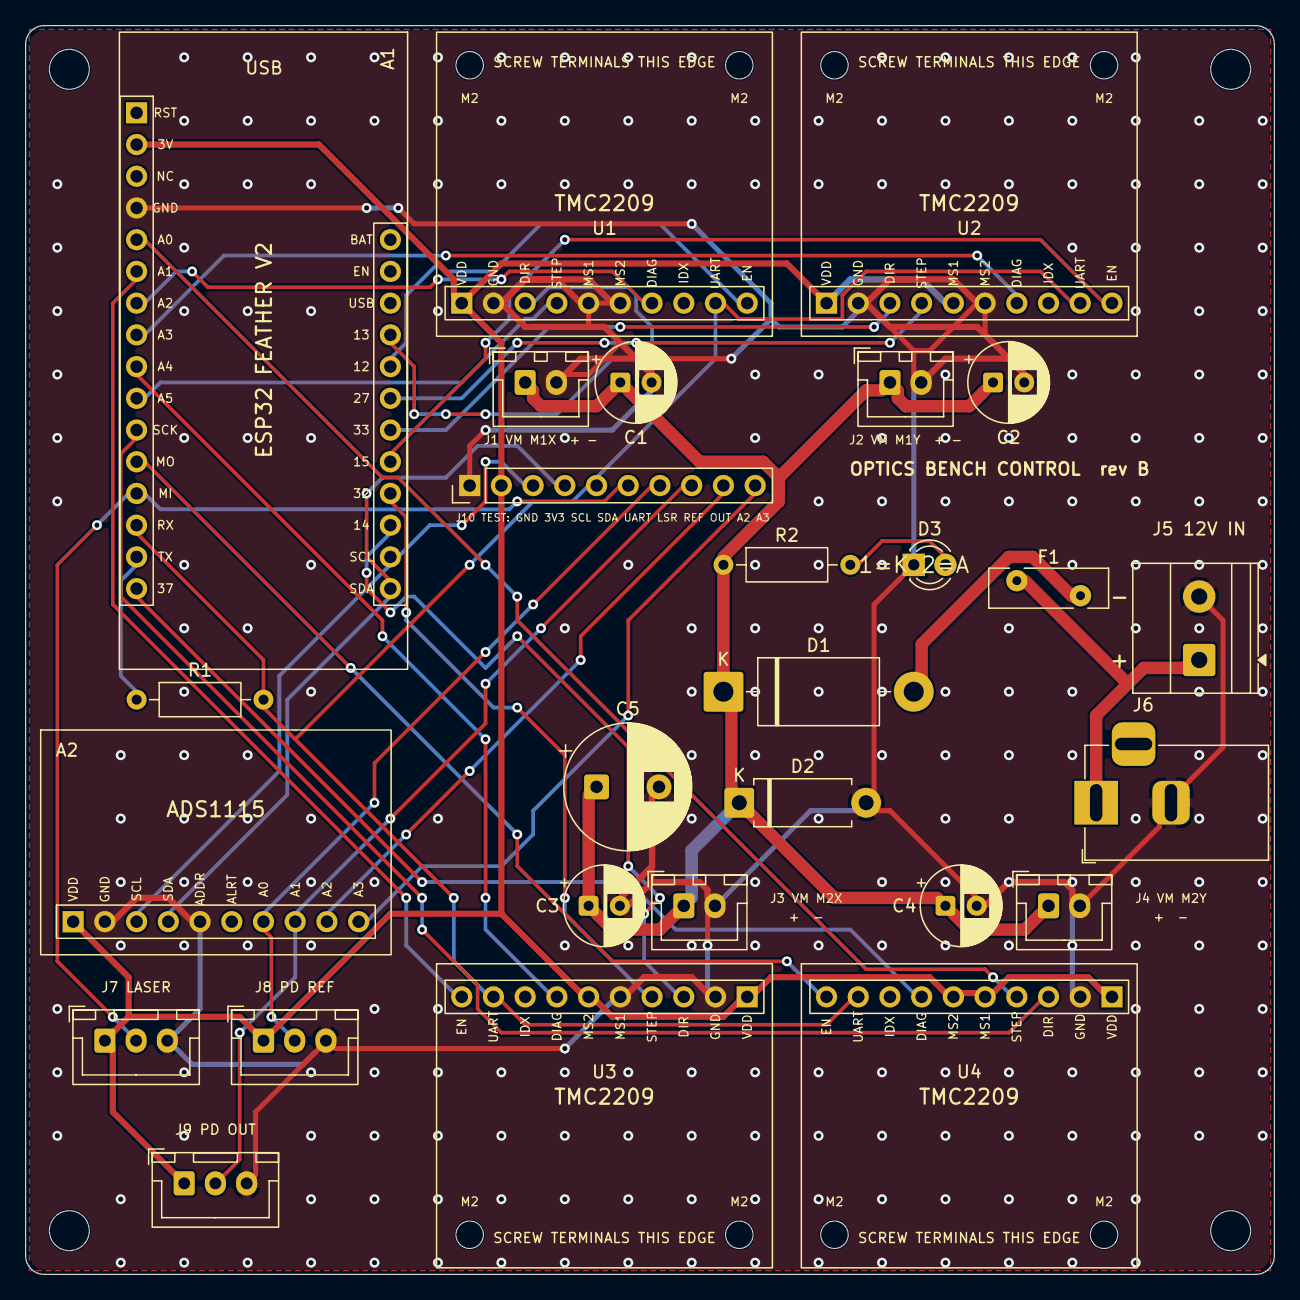
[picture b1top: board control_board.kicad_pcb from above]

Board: 2 copper layers, 100.0 x 100.0 mm, 31 parts (0 on the bottom side), 31 nets.

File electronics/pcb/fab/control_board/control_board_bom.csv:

refs,qty,description,part number,footprint
A1,1,Adafruit ESP32 Feather V2 (on hand),Adafruit 5400,
A2,1,Adafruit ADS1115 breakout,Adafruit 1085,
C1 C2 C3 C4,4,"100 uF 25 V electrolytic, 6.3 mm, 2.5 mm pitch",Panasonic EEU-FR1E101,Capacitor_THT:CP_Radial_D6.3mm_P2.50mm
C5,1,"470 uF 25 V electrolytic, 10 mm, 5 mm pitch",Panasonic EEU-FR1E471,Capacitor_THT:CP_Radial_D10.0mm_P5.00mm
D1,1,"Schottky diode 3 A 40 V, DO-201AD",1N5822,Diode_THT:D_DO-201AD_P15.24mm_Horizontal
D2,1,"TVS 600 W, 15.3 V standoff, bidirectional, DO-15",Littelfuse P6KE18CA,Diode_THT:D_DO-15_P10.16mm_Horizontal
D3,1,3 mm green LED,generic,LED_THT:LED_D3.0mm
F1,1,"PTC resettable fuse, 2 A hold",Bourns MF-RHT200,Fuse:Fuse_Bourns_MF-RHT200
J1 J2 J3 J4,4,"JST-XH 2-pin header, vertical (driver VM feed)",JST B2B-XH-A(LF)(SN),Connector_JST:JST_XH_B2B-XH-A_1x02_P2.50mm_Vertical
J5,1,"Screw terminal 2-pin 5.08 mm (MKDS 1,5/2-5,08)",Phoenix Contact 1729128,"TerminalBlock_Phoenix:TerminalBlock_Phoenix_MKDS-1,5-2-5.08_1x02_P5.08mm_Horizontal"
J6,1,DC barrel jack 5.5 x 2.1 mm,CUI PJ-102AH,Connector_BarrelJack:BarrelJack_Horizontal
J7 J8 J9,3,"JST-XH 3-pin header, vertical",JST B3B-XH-A(LF)(SN),Connector_JST:JST_XH_B3B-XH-A_1x03_P2.50mm_Vertical
J10,1,1x10 male pin header 2.54 mm,generic,Connector_PinHeader_2.54mm:PinHeader_1x10_P2.54mm_Vertical
R1,1,1 kOhm 1/4 W axial,generic,Resistor_THT:R_Axial_DIN0207_L6.3mm_D2.5mm_P10.16mm_Horizontal
R2,1,4.7 kOhm 1/4 W axial,generic,Resistor_THT:R_Axial_DIN0207_L6.3mm_D2.5mm_P10.16mm_Horizontal
U1 U2 U3 U4,4,Adafruit TMC2209 breakout (on hand),Adafruit 6121,
A1 socket,1,"Female header 1x16, 2.54 mm, 8.5 mm tall",generic (e.g. Adafruit 2940 kit),
A1 socket,1,"Female header 1x12, 2.54 mm, 8.5 mm tall",generic (e.g. Adafruit 2940 kit),
U1-U4 sockets,4,"Female header 1x10, 2.54 mm",generic,
U1-U4 standoffs,8,"M2 x 11 mm standoff + 2 M2 screws, under each breakout's terminal-end holes",generic,
J1-J4 VM leads,4,"JST-XH 2-pin lead, about 60 mm, bare ends into the breakout's VM + / - terminals",JST,
A2 socket,1,"Female header 1x10, 2.54 mm",generic,
J7-J9 cables,1,"JST-XH housings (XHP-3) and SXH-001T-P0.6 crimps, or pre-crimped leads",JST,

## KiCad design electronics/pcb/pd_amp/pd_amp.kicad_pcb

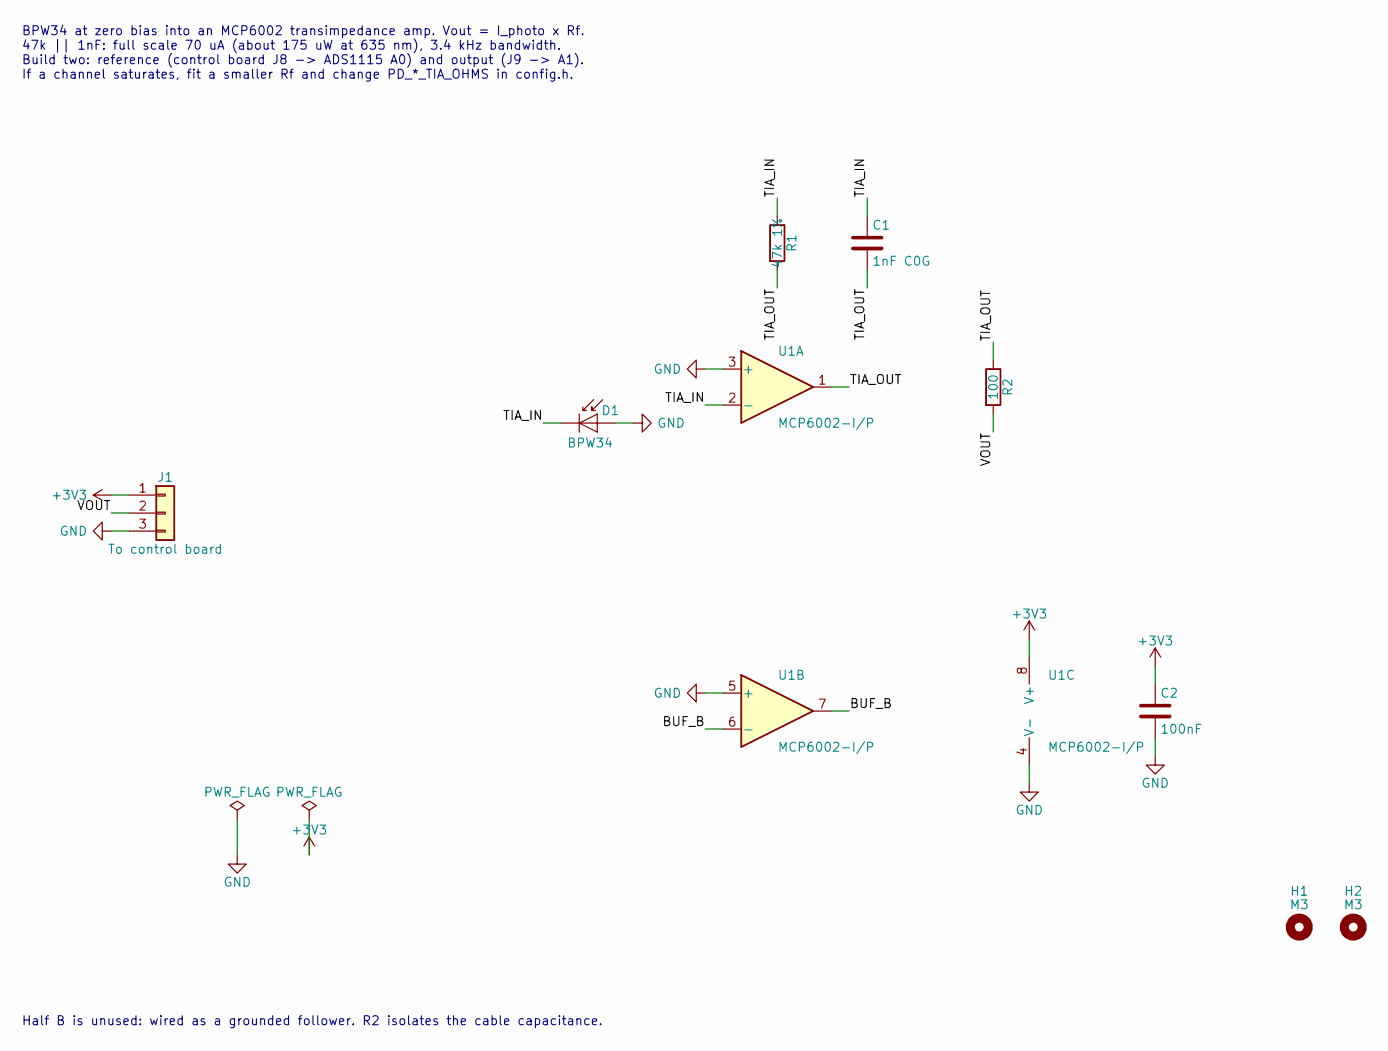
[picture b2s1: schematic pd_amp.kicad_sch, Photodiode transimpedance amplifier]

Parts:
C1: 1nF C0G; C_Disc_D5.0mm_W2.5mm_P5.00mm
C2: 100nF; C_Disc_D5.0mm_W2.5mm_P5.00mm
D1: BPW34; Osram_DIL2_4.3x4.65mm_P5.08mm
H1, H2: M3; MountingHole_3.2mm_M3
J1: To control board; JST_XH_B3B-XH-A_1x03_P2.50mm_Vertical
R1: 47k 1%; R_Axial_DIN0207_L6.3mm_D2.5mm_P7.62mm_Horizontal
R2: 100; R_Axial_DIN0207_L6.3mm_D2.5mm_P7.62mm_Horizontal
U1: MCP6002-I/P; DIP-8_W7.62mm

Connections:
+3V3: C2.1, J1.1, U1.8 (V+)
/BUF_B: U1.6 (-), U1.7
/TIA_IN: C1.1, D1.1 (K), R1.1, U1.2 (-)
/TIA_OUT: C1.2, R1.2, R2.1, U1.1
/VOUT: J1.2, R2.2
GND: C2.2, D1.2 (A), J1.3, U1.3 (+), U1.4 (V-), U1.5 (+)

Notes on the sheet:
BPW34 at zero bias into an MCP6002 transimpedance amp. Vout = I_photo x Rf. 47k || 1nF: full scale 70 uA (about 175 uW at 635 nm), 3.4 kHz bandwidth. Build two: reference (control board J8 -> ADS1115 A0) and output (J9 -> A1). If a channel saturates, fit a smaller Rf and change PD_*_TIA_OHMS in con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
Half B is unused: wired as a grounded follower. R2 isolates the cable capacitance.

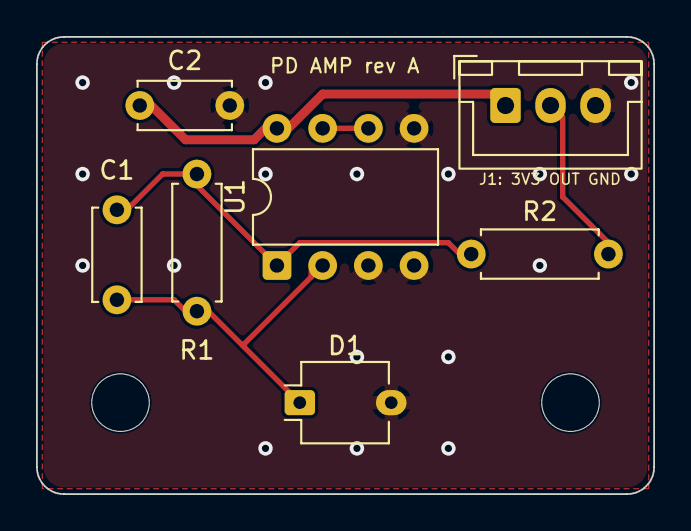
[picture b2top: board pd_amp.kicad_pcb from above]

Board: 2 copper layers, 34.3 x 25.4 mm, 9 parts (0 on the bottom side), 6 nets.

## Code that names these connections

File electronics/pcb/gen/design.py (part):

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            sch=(223.52 + (i % 2) * 91.44, 30.48 + (i // 2) * 71.12), pcb=(*DRIVER_CAP_PCB[i], 0))

    parts["R1"] = dict(lib="Device:R", value="1k", fp="Resistor_THT:R_Axial_DIN0207_L6.3mm_D2.5mm_P10.16mm_Horizontal",
                       pins={"1": "TMC_TX", "2": "TMC_UART"}, sch=(119.38, 139.7), pcb=(8.89, 53.975, 0))

    # 12 V input: screw terminal or barrel jack, PTC fuse, series Schottky for reverse polarity,
    # TVS, bulk capacitor and a power LED.
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                       fp="Connector_BarrelJack:BarrelJack_Horizontal",
                       pins={"1": "VIN", "2": GND}, sch=(30.48, 215.9), pcb=(85.725, 62.23, 180))
    parts["F1"] = dict(lib="Device:Polyfuse", value="MF-RHT200", fp="Fuse:Fuse_Bourns_MF-RHT200",
                       pins={"1": "VIN", "2": "VIN_F"}, sch=(50.8, 190.5), pcb=(79.375, 44.45, 0))
    parts["D1"] = dict(lib="Device:D_Schottky", value="1N5822", fp="Diode_THT:D_DO-201AD_P15.24mm_Horizontal",
                       pins={"1": V12, "2": "VIN_F"}, sch=(73.66, 185.42), pcb=(55.88, 53.34, 0))
    parts["D2"] = dict(lib="Device:D_TVS", value="P6KE18CA", fp="Diode_THT:D_DO-15_P10.16mm_Horizontal",
                       pins={"1": V12, "2": GND}, sch=(83.82, 198.12), pcb=(57.15, 62.23, 0))
    parts["C5"] = dict(lib="Device:C_Polarized", value="470uF 25V", fp="Capacitor_THT:CP_Radial_D10.0mm_P5.00mm",
                       pins={"1": V12, "2": GND}, sch=(109.22, 198.12), pcb=(45.72, 60.96, 0))
    parts["R2"] = dict(lib="Device:R", value="4.7k", fp="Resistor_THT:R_Axial_DIN0207_L6.3mm_D2.5mm_P10.16mm_Horizontal",
                       pins={"1": V12, "2": "LED_12V"}, sch=(127.0, 190.5), pcb=(55.88, 43.18, 0))
    parts["D3"] = dict(lib="Device:LED", value="12V ON (green)", fp="LED_THT:LED_D3.0mm",
                       pins={"1": GND, "2": "LED_12V"}, sch=(127.0, 213.36), pcb=(71.12, 43.18, 0))

    # Off-board connections
    parts["J7"] = dict(lib="Connector_Generic:Conn_01x03", value="Laser",
                       fp="Connector_JST:JST_XH_B3B-XH-A_1x03_P2.50mm_Vertical",
                       pins={"1": V33, "2": "LASER_TTL", "3": GND}, sch=(157.48, 190.5), pcb=(6.35, 81.28, 0))
    parts["J8"] = dict(lib="Connector_Generic:Conn_01x03", value="PD reference",
                       fp="Connector_JST:JST_XH_B3B-XH-A_1x03_P2.50mm_Vertical",
                       pins={"1": V33, "2": "PD_REF", "3": GND}, sch=(157.48, 205.74), pcb=(19.05, 81.28, 0))
    parts["J9"] = dict(lib="Connector_Generic:Conn_01x03", value="PD output",
                       fp="Connector_JST:JST_XH_B3B-XH-A_1x03_P2.50mm_Vertical",
                       pins={"1": V33, "2": "PD_OUT", "3": GND}, sch=(157.48, 220.98), pcb=(12.7, 92.71, 0))
    parts["J10"] = dict(lib="Connector_Generic:Conn_01x10", value="Test (Analog Discovery)",
                        fp="Connector_PinHeader_2.54mm:PinHeader_1x10_P2.54mm_Vertical",
                        pins={"1": GND, "2": V33, "3": "I2C_SCL", "4": "I2C_SDA", "5": "TMC_UART",
                              "6": "LASER_TTL", "7": "PD_REF", "8": "PD_OUT", "9": "AIN2", "10": "AIN3"},
                        sch=(203.2, 200.66), pcb=(35.56, 36.83, 90))
    parts["A2"] = dict(lib="optics_bench:Adafruit_ADS1115_Breakout", value="ADS1115 (0x48)",
                       pins={"1": V33, "2": GND, "3": "I2C_SCL", "4": "I2C_SDA", "5": GND, "6": NC,
                             "7": "PD_REF", "8": "PD_OUT", "9": "AIN2", "10": "AIN3"},
                       sch=(248.92, 200.66), pcb=(3.81, 71.755, 0))
    for n, (x, y) in enumerate([(3.5, 3.5), (96.5, 3.5), (3.5, 96.5), (96.5, 96.5)]):
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    parts = {
        "J1": dict(lib="Connector_Generic:Conn_01x03", value="To control board",
                   fp="Connector_JST:JST_XH_B3B-XH-A_1x03_P2.50mm_Vertical",
                   pins={"1": V33, "2": "VOUT", "3": GND}, sch=(40.64, 88.9), pcb=(26.035, 3.81, 0)),
        "D1": dict(lib="Sensor_Optical:BPW34", value="BPW34", fp="OptoDevice:Osram_DIL2_4.3x4.65mm_P5.08mm",
                   pins={"1": "TIA_IN", "2": GND}, sch=(101.6, 76.2), pcb=(14.605, 20.32, 0)),
        "U1": dict(lib="Amplifier_Operational:MCP6002-xP", value="MCP6002-I/P",
                   fp="Package_DIP:DIP-8_W7.62mm",
                   pins={"1": "TIA_OUT", "2": "TIA_IN", "3": GND, "5": GND, "6": "BUF_B", "7": "BUF_B",
                         "4": GND, "8": V33},
                   sch={1: (127.0, 71.12), 2: (127.0, 116.84), 3: (165.1, 116.84)}, pcb=(13.335, 12.7, 90)),
        "R1": dict(lib="Device:R", value="47k 1%",
                   fp="Resistor_THT:R_Axial_DIN0207_L6.3mm_D2.5mm_P7.62mm_Horizontal",
                   pins={"1": "TIA_IN", "2": "TIA_OUT"}, sch=(127.0, 50.8), pcb=(8.89, 15.24, 90)),
        "C1": dict(lib="Device:C", value="1nF C0G", fp="Capacitor_THT:C_Disc_D5.0mm_W2.5mm_P5.00mm",
                   pins={"1": "TIA_IN", "2": "TIA_OUT"}, sch=(139.7, 50.8), pcb=(4.445, 14.605, 90)),
        "C2": dict(lib="Device:C", value="100nF", fp="Capacitor_THT:C_Disc_D5.0mm_W2.5mm_P5.00mm",
                   pins={"1": V33, "2": GND}, sch=(180.34, 116.84), pcb=(5.715, 3.81, 0)),
        "R2": dict(lib="Device:R", value="100", fp="Resistor_THT:R_Axial_DIN0207_L6.3mm_D2.5mm_P7.62mm_Horizontal",
                   pins={"1": "TIA_OUT", "2": "VOUT"}, sch=(157.48, 71.12), pcb=(24.13, 12.065, 0)),
        "H1": dict(lib="Mechanical:MountingHole", value="M3", fp="MountingHole:MountingHole_3.2mm_M3",
                   pins={}, sch=(200.66, 147.32), pcb=(4.645, 20.32, 0)),
        "H2": dict(lib="Mechanical:MountingHole", value="M3", fp="MountingHole:MountingHole_3.2mm_M3",
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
